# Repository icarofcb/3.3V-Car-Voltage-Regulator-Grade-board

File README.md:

# 3V3-REGULATOR — Design Notes

**Project:** Automotive-grade 9 V–15 V to 3.3 V / 500 mA power supply
**Author:** Icaro (github.com/icarofcb)
**Tool:** KiCad 10.0.4 · 2-layer PCB
**Rev:** 1 · 2026-06-28

---

## 1. Overview

This board converts an unregulated automotive DC bus (9 V–15 V) into a clean, regulated **3.3 V rail at up to 500 mA**, with the input, the converter, and the load protected end to end. The signal path is:

```
J2 (9–15 V) → [Protected Input: fuse + ferrite + flat-clamp TVS + bulk caps]
            → [Synchronous Buck: LMR33630BDDA @ 1.4 MHz]
            → [Smart Fuse: TPS25200 eFuse, current limit + OV clamp + fault flag]
            → J9 (3.3 V protected output)
```

Visual diagnostics (power-good and fault LEDs) and four mounting holes are provided for integration and bring-up.

---

## 2. Electrical Specifications

| Parameter | Specification | As-designed |
|---|---|---|
| Input voltage | 9 V – 15 V DC | 9 V – 15 V (LMR33630: 3.8 V–36 V) |
| Output voltage | 3.3 V DC | 3.315 V (FB divider 100 k / 43.2 k) |
| Output current | 500 mA max | eFuse limit ≈ 1.43 A typ (margin) |
| Output power | 1.65 W | 1.65 W |
| Topology | Candidate's choice | **Synchronous buck** (justified §3) |
| Switching frequency | — | 1.4 MHz (LMR33630**B**DDA) |
| Estimated efficiency | State | **≈ 86–88 %** @ 12 V, 0.5 A (§5) |
| Target ripple | State | **< 20 mV pk-pk** (est. ~5 mV, §6) |

---

## 3. Topology Selection & Justification

**Chosen: synchronous step-down (buck) converter.**

A linear regulator (LDO) was rejected on thermal grounds. Dropping 12 V → 3.3 V at 0.5 A in a linear pass element dissipates `(12 − 3.3) × 0.5 = 4.35 W`, and at the 15 V corner `(15 − 3.3) × 0.5 = 5.85 W`. That is an efficiency of only 22–28 % and several watts to remove from a small 2-layer board with no dedicated copper plane — not viable.

A synchronous buck reaches ~85–90 % at this operating point, dissipating only a few hundred mW. The **LMR33630BDDA** was selected because it:

- Covers the full input range with wide margin (3.8 V–36 V vs. 9–15 V), tolerating load-dump ride-through above 15 V.
- Integrates both MOSFETs (synchronous), removing the external catch diode and its loss.
- Switches at **1.4 MHz**, which shrinks the inductor (2.2 µH) and output caps and places the switching fundamental above the AM band, easing conducted-EMI compliance.
- Is marketed as an "ultra-low EMI" SIMPLE SWITCHER in an SO PowerPAD package with low parasitic loop inductance.
- Has an internally compensated, peak-current-mode loop — minimal external part count, robust across line/load.

---

## 4. Functional Block Description

### 4.1 Protected Input Stage

| Ref | Part | Role |
|---|---|---|
| F1 | SF-1206HHA1000R-2 | Board input fuse — hard-fault / short protection. Note on schematic: can be replaced by an automotive blade fuse. |
| L1 | Ferrite 26 Ω @ 100 MHz, 10 A | Series element of the input EMI filter (conducted-emissions / di-dt damping). |
| IC1 | TVS1800DRVR | Flat-clamp surge protection (load-dump / ISO 7637-style transients), 18 V standoff. |
| C1 | 47 µF | Bulk input hold-up. |
| C2, C21 | 10 µF 50 V | Buck input decoupling (high-frequency hot-loop caps). |
| C3, C4, C22, C24 | 0.1 µF | Local HF bypass. |
| C29 | 1 µF | Protected-rail decoupling. |

The fuse, ferrite, and bulk/HF caps form a **pi (C–L–C) input filter**: the ferrite blocks the switcher's di/dt from the harness while the caps supply the pulsed input current locally. The TVS1800 shunts surge energy and clamps flat, with an 18 V standoff that sits comfortably above the 15 V input corner.

### 4.2 Buck Regulator

| Ref | Part | Role |
|---|---|---|
| U2 | LMR33630BDDA | 1.4 MHz synchronous buck, 3.8–36 V in, 3 A. |
| L4 | 2.2 µH | Power inductor. |
| R8 / R9 | 100 k / 43.2 k | Feedback divider → V_OUT = 1.0 V × (1 + 100/43.2) = **3.315 V**. |
| C30 | 0.1 µF | Bootstrap (BOOT–SW). |
| C5 / C7 | 1 µF | VCC / local decoupling. |
| C34, C35, C37, C38, C42 | 10 µF 50 V | Output capacitor bank (3.3 V rail). |

The 1.0 V internal reference and the 100 k / 43.2 k divider set 3.315 V (+0.5 %, within tolerance). The output bank is deliberately conservative for low ripple and good transient response; effective capacitance after DC-bias derating is well below the 50 µF nominal but still ample for this load.

### 4.3 Output Smart Fuse (eFuse)

| Ref | Part | Role |
|---|---|---|
| IC2 | TPS25200DRVR | eFuse: adjustable current limit, OV clamp, OVLO, thermal, reverse blocking, fault flag. |
| R11 | 68 k | R_ILIM → current-limit threshold. |
| D8, D9 (blue) | Power-good indicators | Lit on healthy 3.3 V. |
| D10 (red) | Fault indicator | Driven by FAULT (open-drain). |
| R15, R17 (220 Ω), R16 (1 k) | LED / pull-up resistors | |
| J9 | 282834-2 | Protected 3.3 V output. |

`R_ILIM = 68 kΩ` sets a current-limit threshold of **≈ 1.43 A typ** (≈ 1.30 A min / 1.55 A max over tolerance from the datasheet I_OS equations). That sits comfortably above the 500 mA spec and even above a 1 A transient peak, while still cutting off hard on a downstream short. The TPS25200 also provides an output OV **clamp at ~5.4 V** and **OVLO shutoff at 7.6 V V_IN**, so a failed buck high-side FET dumping the raw input onto the 3.3 V rail is disconnected from the load rather than passed through. The open-drain FAULT asserts on over-current, over-temperature, or over-voltage and drives the red LED — no microcontroller required.

---

## 5. Efficiency Estimate

At 12 V → 3.3 V, 0.5 A, the LMR33630 (1.4 MHz variant) operates around **87 %** per its characteristic curves. The series eFuse adds `60 mΩ × 0.5 A = 30 mV` drop → `~0.9 %` loss. Net **≈ 86 %** at nominal.

Trend across the input range (switching loss scales with V_IN):

| V_IN | Est. converter η | Net (incl. eFuse) |
|---|---|---|
| 9 V | ~89 % | ~88 % |
| 12 V | ~87 % | ~86 % |
| 15 V | ~85 % | ~84 % |

Total dissipation at the worst corner is on the order of a few hundred mW, spread across U2's PowerPAD and L4 — manageable on 2 layers with a stitched ground pour and a thermal-via array under the IC.

---

## 6. Ripple Budget

**Inductor ripple current** (`ΔI_L = V_OUT·(V_IN−V_OUT)/(V_IN·L·f_sw)`):

- 12 V: `3.3 × 8.7 / (12 × 2.2µ × 1.4M) ≈ 0.78 A` pk-pk
- 15 V (worst): `≈ 0.84 A` pk-pk
- Peak inductor current at 0.5 A load: `0.5 + 0.42 ≈ 0.92 A` — far below L4 / U2 limits.

**Output voltage ripple** (ceramic bank, ESR negligible, `ΔV ≈ ΔI_L/(8·f_sw·C_OUT)`):

- With ~40 µF effective: `0.84 / (8 × 1.4M × 40µ) ≈ 2 mV` pk-pk.

**Target: < 20 mV pk-pk**; estimated **~5 mV** including ESL/ESR margin. Input ripple is held down by C1/C2/C21 plus the L1 ferrite (pi filter).

---

## 7. Automotive Best Practices

**Protection (layered):**
1. Input hard-fault / short → F1 (replaceable by a blade fuse, coordinated with the vehicle supply).
2. Surge / load-dump transients → TVS1800 flat clamp (18 V standoff, clamps surge below ~25 V — well under the LMR33630 36 V abs-max and the 50 V cap rating).
3. Output over-current / short / OV / reverse → TPS25200 eFuse with auto-recovery and fault flag.
4. Visual go/no-go → power-good (blue) and fault (red) LEDs.

**EMI / EMC:**
- 1.4 MHz fundamental keeps key harmonics out of the AM band.
- Pi input filter (C–ferrite–C) attenuates conducted emissions on the harness.
- Tight switching hot loop and small SW-node copper minimize radiated emissions.
- TVS + bulk caps address surge immunity (IEC 61000-4-5 class) and EFT/ESD on the input.
- Exposed gold perimeter ring bonds PCB ground to the aluminum enclosure (360° chassis bond), extending the shield to the case.

**Power / Signal Integrity:**
- Output cap bank close to the load connector for low rail impedance and good step-load response.
- Feedback divider routed away from the SW node; FB tap taken at the point of regulation.
- Unbroken bottom-layer ground plane as the reference and lowest-impedance return for every net.

**DFM / DFT / DFA:**
- DFM: assembly-friendly 1206/0603 passives, standard footprints, thermal-via arrays under U2 and IC2, generous clearances for a 2-layer process.
- DFT: test points on V_IN, 3.3 V, FAULT, and GND; FAULT net brought out; LEDs give instant powered diagnostics; output on a keyed connector for in-line current measurement.
- DFA: polarized 282834-2 connectors (no reverse mating), consistent passive orientation, four mounting holes (H1–H4) for mechanical fixturing and vibration robustness.

---

## 8. 2-Layer PCB Layout Strategy

The stackup is deliberately simple and EMC-driven: **the top layer carries all signals and power; the bottom layer is an unbroken ground plane.** On a 2-layer board this is the single biggest lever for EMC and integrity — every trace on top runs over continuous reference copper, so each signal's return current flows in the image directly beneath it, giving the smallest possible loop area and a clean, low-impedance return for every net.

- **Solid ground plane (bottom):** the entire second layer is ground, with no splits or cutouts. Nothing signal or power is routed on the bottom, because any trace there would slot the plane and force return current to detour around it (added loop area → radiated emissions and ground bounce).
- **Input hot loop** (C2/C21 → VIN → GND) kept physically tiny on top — it carries the highest di/dt — with its ground return dropped straight into the plane through vias at the cap pads.
- **SW node** copper minimized in area (radiator) but wide enough for current; inductor placed immediately at SW.
- **Returns / stitching:** a ground via at every ground pad ties each device to the plane with minimal inductance; vias along the high-current return path keep impedance low.
- **Chassis-bond shield ring:** an exposed (soldermask-free), gold-finished (ENIG) ground ring runs around the board perimeter and is via-stitched to the bottom plane, so it bonds PCB ground to the aluminum enclosure around the full edge. Gold keeps the contact low-resistance and corrosion-free under compression and vibration (bare copper would oxidize into an unreliable joint). The 360° bond extends the Faraday shield onto the case, improving radiated emissions and immunity, and gives a short chassis return path for ESD/surge.
- **Thermal:** U2 PowerPAD and IC2 EP drop into the bottom ground copper through via arrays, using the full plane as the heat-spreader.
- **Output caps** hugging the inductor output and the eFuse input; protected-rail caps near J9.
- **Sensitive nets** (FB, ILIM) kept short over solid ground, away from SW and the inductor field.
- **Input protection** (F1, L1, TVS1800) placed at the connector edge so transient energy is shunted before it propagates onto the board.

---

## 9. Component Selection Notes

- **Decoupling / bulk MLCCs:** specified as Murata **GCM** series (AEC-Q200, X7R, −55…+125 °C). For positions in 0805 and larger, or anywhere board flex/vibration is a concern, the **GCJ** soft-termination equivalents are the preferred upgrade (conductive-polymer layer that absorbs board-bending stress and prevents flex cracks).
- **10 µF / 50 V / 1206:** only available as **X7T** in this size/voltage (e.g. GCM31CD71H106KE36L) — note the wider temperature/DC-bias characteristic vs. X7R and the heavy DC-bias derating on the 9–15 V input cap (C2).
- **Voltage derating:** 50 V ceramics on a 3.3 V rail and on the 12 V bus keep stress well inside ECSS/IPC-style derating; the 1 µF/0603 parts are 25 V (fine on 3.3 V/5 V nodes, re-evaluate if any sits on the raw 9–15 V bus).
- **eFuse R_ILIM = 68 kΩ** verified against the TPS25200 datasheet I_OS equations (not just the table): min ≈ 1.30 A stays clear of the load; max ≈ 1.55 A gives a defined cut-off.

---

## 10. Submitted Files

| File | Description |
|---|---|
| `3v3-regulator.kicad_pro` | KiCad project |
| `3v3-regulator.kicad_sch` | Schematic |
| `3v3-regulator.kicad_pcb` | 2-layer PCB layout |
| `README` / Design Notes | This document |

## 11. Extra Files

The `manufacture files` directory holds the full output set: design notes, fabrication/manufacturing files, and the schematic export. Gerbers and the schematic source are also available in the `gerber/` and `Schematic/` directories.

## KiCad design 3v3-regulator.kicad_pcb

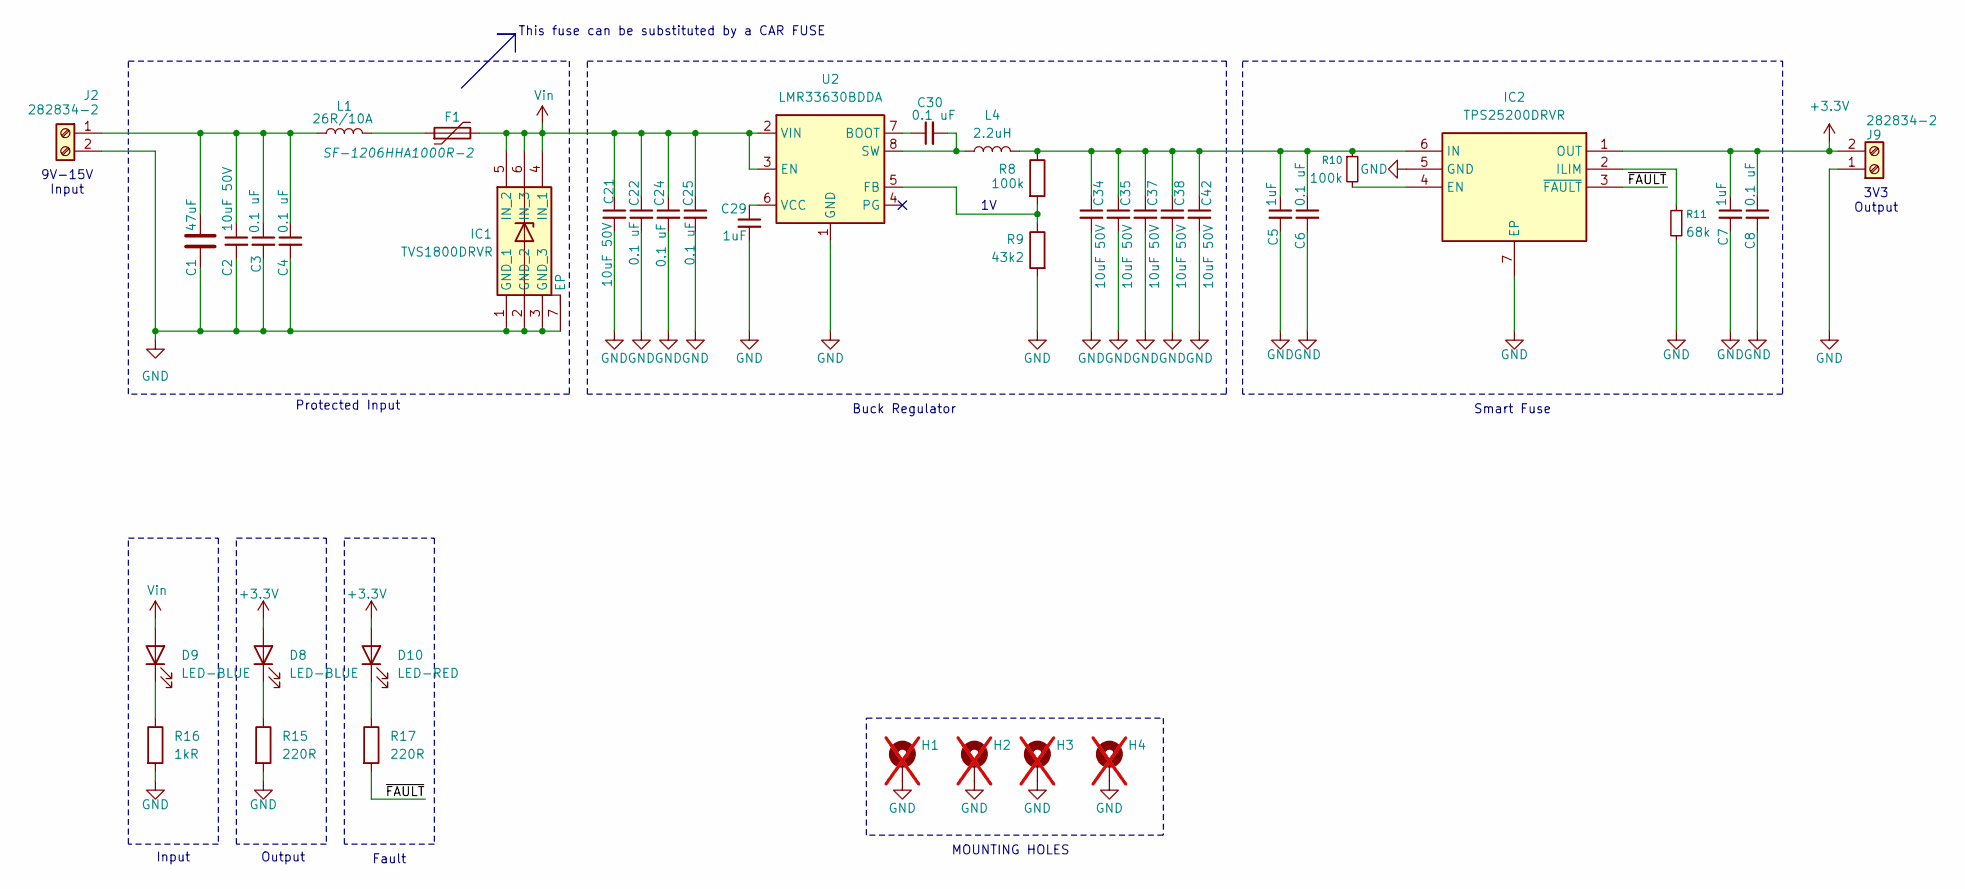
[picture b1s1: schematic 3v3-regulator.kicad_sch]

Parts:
C1: 47uF; CAPC6050X350N; MPN KRM55WR71H476MH13K; Digi-Key_PN 445-174690-6-ND
C2, C21, C34, C35, C37, C38, C42: 10uF 50V; C_1206_3216Metric; MPN GCM31CD71H106KE36L; LCSC-PN C13585
C3, C4, C6, C8, C22, C24, C25, C30: 0.1 uF; C_0603_1608Metric; MPN GCM188R71H104KA57D; LCSC-PN C106256
C5, C7: 1uF; C_0603_1608Metric; MPN GCM188R71E105KA64D
C29: 1uF; C_0603_1608Metric; MPN GCM188R71E105KA64D; Digi-Key_PN 490-13409-6-ND
D8, D9: LED-BLUE; LED_0603_1608Metric; MPN 599-0090-137F
D10: LED-RED; LED_0603_1608Metric; MPN 599-0010-137F
F1: SF-1206HHA1000R-2; Fuse_1206_3216Metric; MPN SF-1206HHA1000R-2; Mouser Part Number 652-SF-1206HHA1000R2
H1, H2, H3, H4: MountingHole_Pad; MountingHole_3.2mm_M3_DIN965_Pad; not fitted
IC1: TVS1800DRVR; SON65P200X200X80-7N; MPN TVS1800DRVR
IC2: TPS25200DRVR; SON65P200X200X80-7N; Mouser Part Number 595-TPS25200DRVR
J2, J9: 282834-2; TerminalBlock_TE_282834-2_1x02_P2.54mm_Horizontal; MPN 282834-2
L1: 26R/10A; L_1210_3225Metric; MPN BLE32PN260SH1L; Mouser Part Number 81-BLE32PN260SH1L
L4: 2.2uH; INDPM4441X120N; MPN SRP4012TA-2R2M; Mouser Part Number 652-SRP4012TA-2R2M
R8: 100k; R_0603_1608Metric; MPN AA0603FR-07100KL; LCSC-PN C25741
R9: 43k2; R_0603_1608Metric; MPN ERA-3AEB4322V; Mouser Part Number 667-ERA-3AEB4322V
R10: 100k; R_0603_1608Metric; MPN AA0603FR-07100KL
R11: 68k; R_0603_1608Metric; MPN ERA-3AEB683V
R15, R17: 220R; R_0603_1608Metric; MPN AC0603FR-07220RL
R16: 1kR; R_0603_1608Metric; MPN AA0603FR-071KL
U2: LMR33630BDDA; Texas_HSOP-8-1EP_3.9x4.9mm_P1.27mm_ThermalVias; MPN LMR33630BDDA; Mouser Part Number 595-LMR33630BDDA

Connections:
+3.3V: C7.1, C8.1, D8.2 (A), D10.2 (A), IC2.1 (OUT), J9.2
/~FAULT: IC2.3 (~FAULT), R17.2
GND: C1.2, C2.2, C3.2, C4.2, C5.2, C6.2, C7.2, C8.2, C21.2, C22.2, C24.2, C25.2, C29.2, C34.2, C35.2, C37.2, C38.2, C42.2, H1.1 (1_1), H2.1 (1_1), H3.1 (1_1), H4.1 (1_1), IC1.1 (GND_1), IC1.2 (GND_2), IC1.3 (GND_3), IC1.7 (EP), IC2.5 (GND), IC2.7 (EP), J2.2, J9.1, R9.2, R11.2, R15.2, R16.2, U2.1 (GND), U2.9 (GND)
unnamed: D8.1 (K), R15.1
unnamed: D9.1 (K), R16.1
unnamed: D10.1 (K), R17.1
unnamed: F1.1, L1.2
unnamed: IC2.4 (EN), R10.2
unnamed: IC2.2 (ILIM), R11.1
unnamed: C5.1, C6.1, C34.1, C35.1, C37.1, C38.1, C42.1, IC2.6 (IN), L4.2, R8.1, R10.1
unnamed: C1.1, C2.1, C3.1, C4.1, J2.1, L1.1
unnamed: C30.1, U2.7 (BOOT)
unnamed: R8.2, R9.1, U2.5 (FB)
unnamed: C30.2, L4.1, U2.8 (SW)
unnamed: C29.1, U2.6 (VCC)
Vin: C21.1, C22.1, C24.1, C25.1, D9.2 (A), F1.2, IC1.4 (IN_1), IC1.5 (IN_2), IC1.6 (IN_3), U2.2 (VIN), U2.3 (EN)

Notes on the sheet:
MOUNTING HOLES
Buck Regulator
Input
Fault
This fuse can be substituted by a CAR FUSE
Output
9V-15V Input
3V3 Output
Protected Input
Smart Fuse

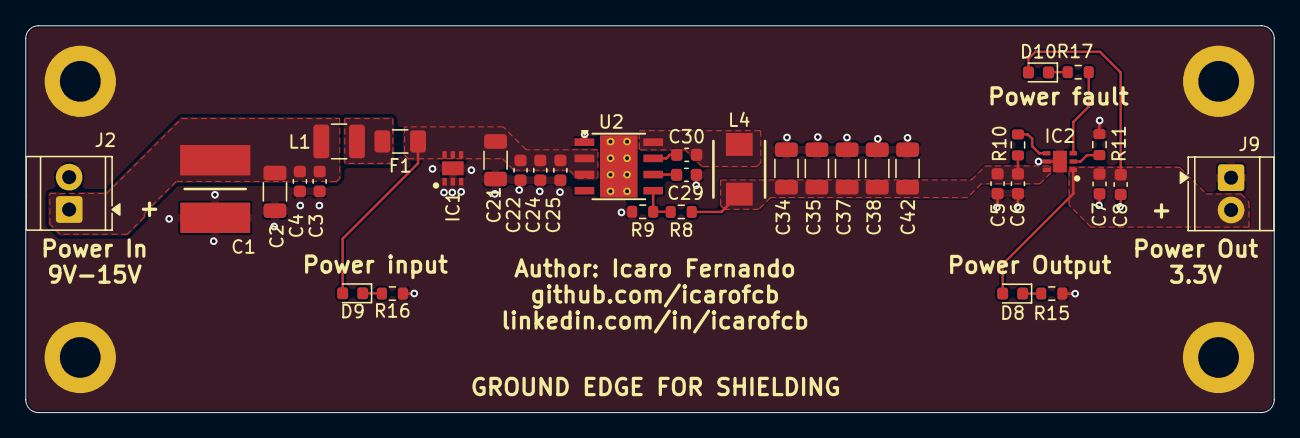
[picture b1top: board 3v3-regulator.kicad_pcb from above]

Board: 2 copper layers, 98.1 x 30.4 mm, 41 parts (0 on the bottom side), 16 nets.

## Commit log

2026-06-29 Pushing design
2026-06-29 Update README with extra files section
    Added section for extra files and their descriptions.
